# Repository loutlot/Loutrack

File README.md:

# Real-Time 3D Tracking System

**English:**  
This project is a work-in-progress real-time 3D tracking system designed to operate with multiple Raspberry Pi cameras. The system is capable of capturing and tracking 3D coordinates using a network of Raspberry Pi 5 devices with Picamera2, which communicate with a central host PC.

**日本語:**  
このプロジェクトは、複数のRaspberry Piカメラを使用してリアルタイムで3Dトラッキングを行うシステムです。Raspberry Pi 5デバイスとPicamera2を使用し、中央ホストPCと通信しながら3D座標をキャプチャおよびトラッキングすることができます。現在、制作中です。

## Project Structure / プロジェクト構成

**English:**  
The project consists of scripts for both the host PC and the Raspberry Pi camera devices. Each script is responsible for a specific part of the system, as described below:

**日本語:**  
このプロジェクトは、ホストPCとRaspberry Piカメラデバイスのためのスクリプトで構成されています。各スクリプトは、以下に説明するように、システムの特定の部分を担当します。

### Host PC Scripts / ホストPCのスクリプト

- **`send_settings.py`**  
  **English:** Sends configuration settings to all Raspberry Pi devices via broadcast.  
  **日本語:** 設定情報をブロードキャストで全Raspberry Piデバイスに送信します。

- **`calibration_host.py`**  
  **English:** Triggers the Raspberry Pi cameras to capture images for calibration, and processes the data to calibrate the system.  
  **日本語:** キャリブレーションのためにRaspberry Piカメラに画像キャプチャをトリガーし、システムのキャリブレーションを行います。

- **`live_tracking_host.py`**  
  **English:** Performs real-time 3D tracking based on the calibrated data and incoming data from the Raspberry Pi cameras.  
  **日本語:** キャリブレーションデータとRaspberry Piカメラからのデータに基づいて、リアルタイムの3Dトラッキングを行います。

### Raspberry Pi Camera Scripts / Raspberry Piカメラスクリプト

- **`receive_settings.py`**  
  **English:** Receives configuration settings from the host and manages the start/stop of the capture process.  
  **日本語:** ホストから設定情報を受信し、キャプチャプロセスの開始/停止を管理します。

- **`capture_script.py`**  
  **English:** Captures images based on the received settings and sends the processed data back to the host for tracking.  
  **日本語:** 受信した設定に基づいて画像をキャプチャし、処理されたデータをホストに送信してトラッキングを行います。

## Work in Progress / 制作中

**English:**  
Please note that this project is still under development. Some features may be incomplete or subject to change. Contributions and feedback are welcome.

**日本語:**  
このプロジェクトは現在開発中であることにご注意ください。一部の機能は未完成であるか、変更される可能性があります。貢献やフィードバックを歓迎します。

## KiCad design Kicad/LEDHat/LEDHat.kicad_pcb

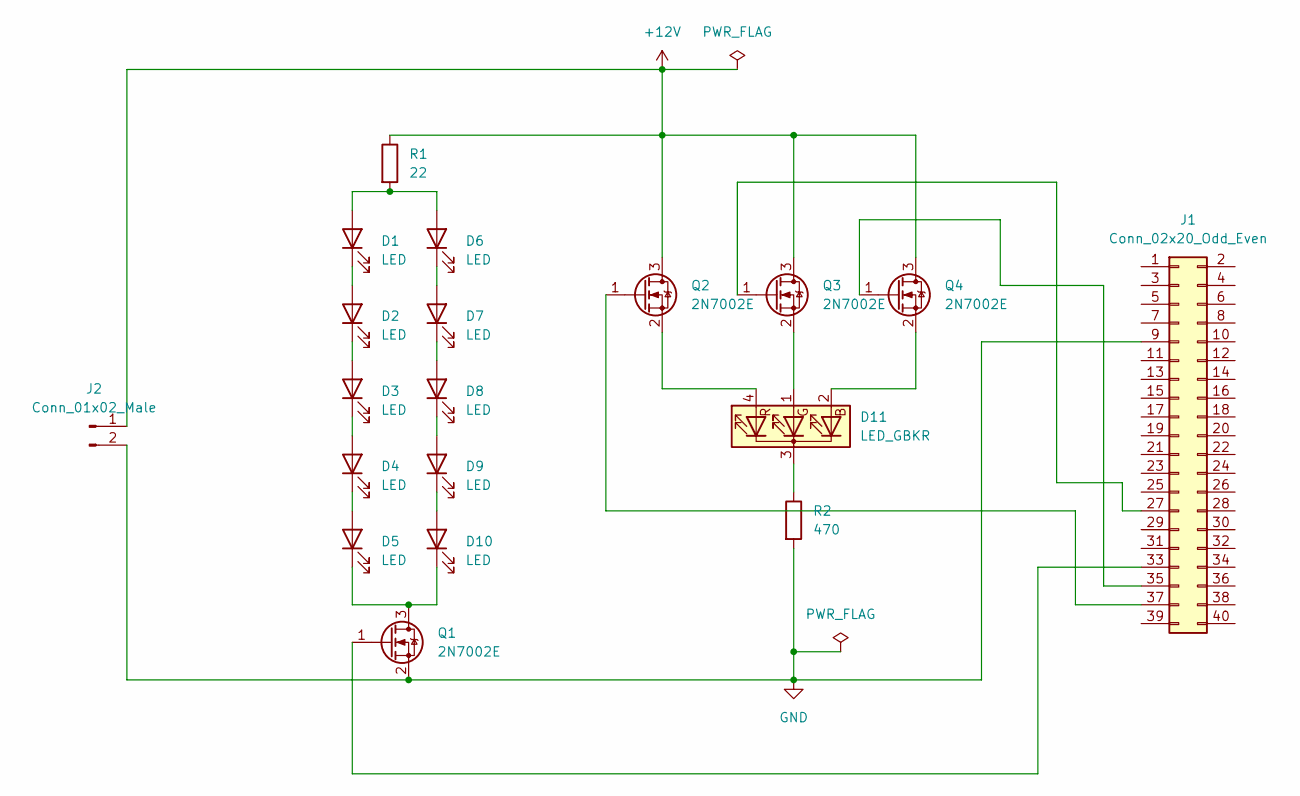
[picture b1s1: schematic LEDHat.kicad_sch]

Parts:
D1, D2, D3, D4, D5, D6, D7, D8, D9, D10: LED; LED_PLCC_2835_Handsoldering
D11: LED_GBKR; LED_D5.0mm-4_RGB_Staggered_Pins
J1: Conn_02x20_Odd_Even; PinSocket_2x20_P2.54mm_Vertical
J2: Conn_01x02_Male; PinHeader_1x02_P2.54mm_Horizontal
Q1, Q2, Q3, Q4: 2N7002E; SOT-23
R1: 22; R_Axial_DIN0207_L6.3mm_D2.5mm_P7.62mm_Horizontal
R2: 470; R_Axial_DIN0207_L6.3mm_D2.5mm_P7.62mm_Horizontal

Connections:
+12V: J2.1, Q2.3 (D), Q3.3 (D), Q4.3 (D), R1.1
GND: J1.9, J2.2, Q1.2 (S), R2.2
unnamed: D1.1 (K), D2.2 (A)
unnamed: D1.2 (A), D6.2 (A), R1.2
unnamed: D2.1 (K), D3.2 (A)
unnamed: D3.1 (K), D4.2 (A)
unnamed: D4.1 (K), D5.2 (A)
unnamed: D6.1 (K), D7.2 (A)
unnamed: D7.1 (K), D8.2 (A)
unnamed: D8.1 (K), D9.2 (A)
unnamed: D5.1 (K), D10.1 (K), Q1.3 (D)
unnamed: D9.1 (K), D10.2 (A)
unnamed: D11.1 (GA), Q3.2 (S)
unnamed: D11.2 (BA), Q4.2 (S)
unnamed: D11.3 (K), R2.1
unnamed: D11.4 (RA), Q2.2 (S)
unnamed: J1.27, Q3.1 (G)
unnamed: J1.33, Q1.1 (G)
unnamed: J1.35, Q4.1 (G)
unnamed: J1.37, Q2.1 (G)

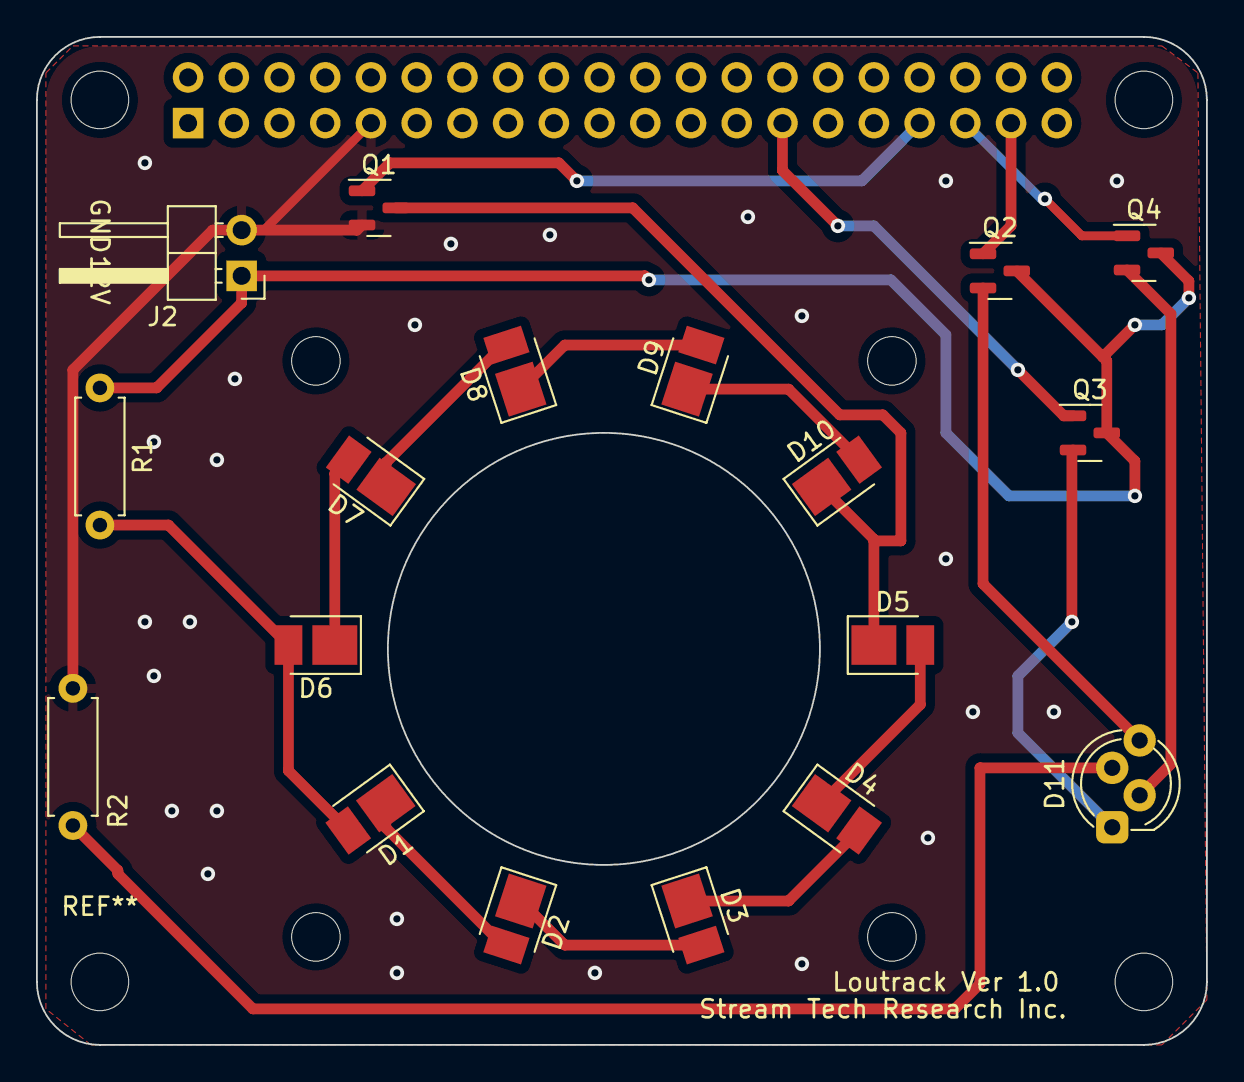
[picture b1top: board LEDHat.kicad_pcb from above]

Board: 2 copper layers, 65.0 x 56.0 mm, 19 parts (1 on the bottom side), 20 nets.

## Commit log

2024-08-31 added PCB Design
2024-08-31 3DModelを追加。 3Dmodel read meを追加。
2024-08-31 3dModelを追加
2024-08-31 Added PCB Design File
